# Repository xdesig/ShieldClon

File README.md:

# ShieldClon V 0.00 and 0.01 

## initial versions.

SlieldClon is a board designed, specifically for mClon. It allows secure connections to manipulate the robot. It has the basic components for its operation, as well as access to all free connections to be able to add new elements. The robot with ShieldClon feeds through a 18650 Li-ion battery 3.7V, which you can recharge through the board.
This plate can be complicated to weld by students that do not have much experience, since it has many components and pins very together, but it is a good challenge to learn.
From the mClon team, we consider it important that students understand the robot's internal functioning, who knows their components and what their function is, so we recommend starting from 4th of ESO not to give the plate already welded, unless previously practiced with protoShield. However, shieldClon can be a good option for work with younger students, always inviting them to connect the sensors and actresses on the shield pins themselves.
Is valid to be able to carry out many STEM projects based on Arduino

![RENDER]

### [Assembly manual][Man]
#### Deseñado en Estrimia con agarimo.

## Author and license
* Author: [XDeSIG][TWI01]
* License:
  CERN Open Hardware Licence Version 2 - Weakly Reciprocal"CERN-OHL-W"
  Doc. Attribution-ShareAlike 4.0 International "CCBY-SA4.0"

## More info:
[tecnoloxia.org]
## To buy boards

Developer don't produce boards to sell. Under [_provider_][provider]
directory there are instructions to order yourself.

<!-- links -->
[tecnoloxia.org]: https://tecnoloxia.org/mclon/que-e-mclon/
[CCBY-SA4.0]: http://creativecommons.org/licenses/by-sa/4.0/
[TWI01]: https://twitter.com/xdesig
[RENDER]: https://github.com/xdesig/ShieldClon/blob/master/img/ShieldClon_0_01_34.png
[provider]: https://www.pcbway.com/project/shareproject/W50475ASJ144_NanoClon_001_gerber_f511f448.html
[Man]: https://github.com/xdesig/ShieldClon/blob/master/ShieldClon_0_00/Montaxe_ShielClon.pdf

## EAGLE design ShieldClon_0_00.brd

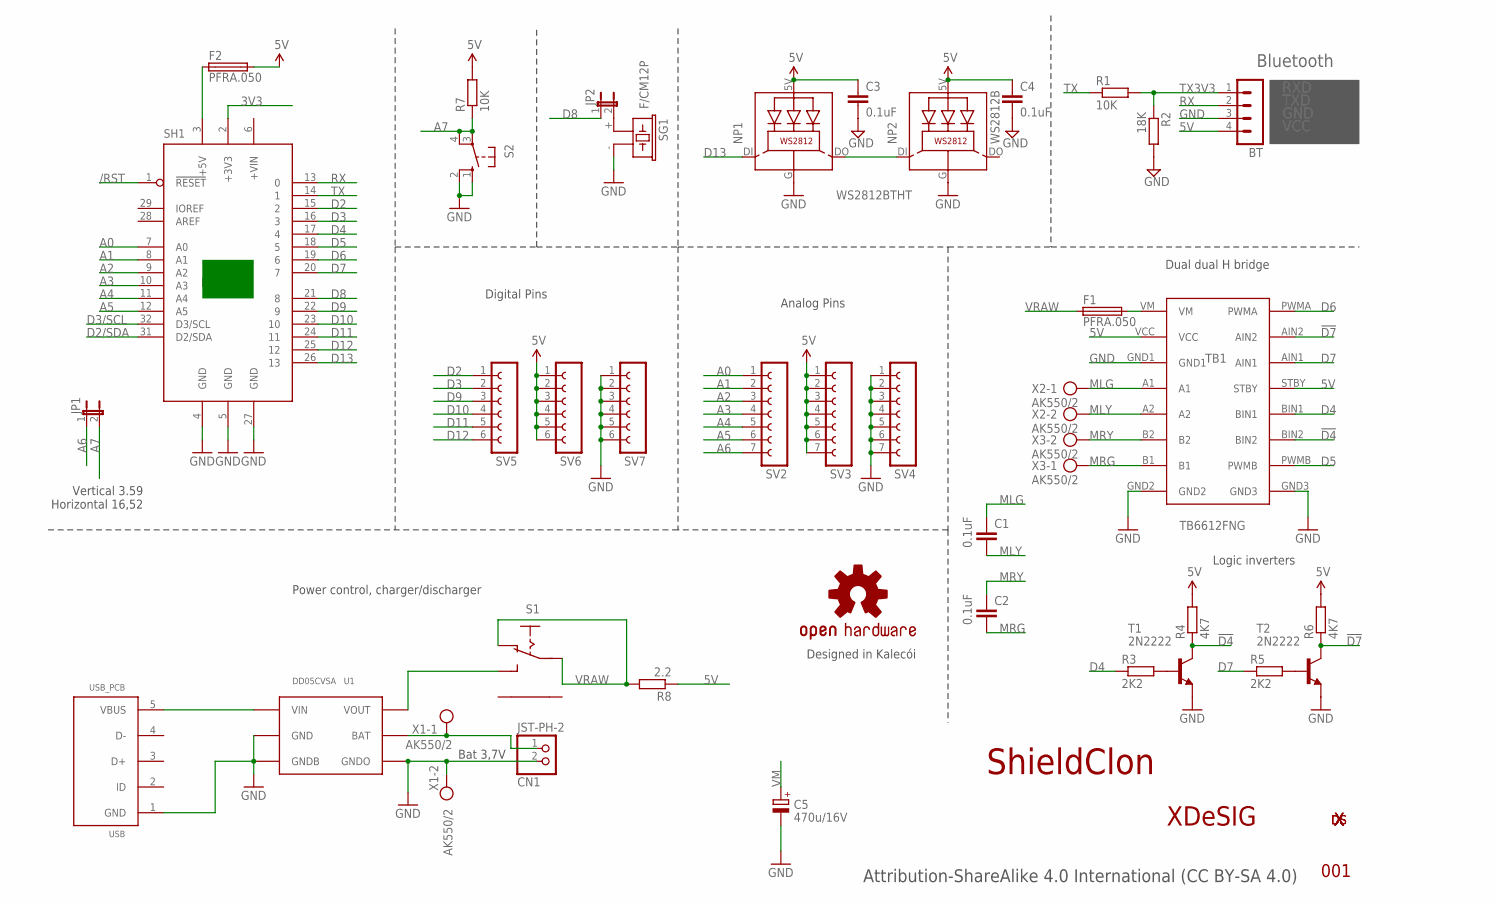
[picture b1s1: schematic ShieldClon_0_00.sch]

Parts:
BT: MA04-1
C1, C2, C3, C4: 0.1uF; C050-024X044
C5: 470u/16V; E2,5-7
CN1: JST-PH-2; JST-PH-2-THM-RA
F1, F2: PFRA.050; TE5
JP1: JP1E; JP1
JP2: JUMPER_JP1E; JUMPER_JP1
LOGO4: OSHW-LOGOS; OSHW-LOGO-S
NP1: WS2812BTHT; NEOPIXEL5MM
NP2: WS2812B; NEOPIXEL5MM
R1, R7: 10K; 0204/7
R2: 18K; 0204/7
R3, R5: 2K2; 0204/7
R4, R6: 4K7; 0204/7
R8: 2.2; 0204/7
S1: ESCORNA_SK12F14D; ESCORNA_SK-12D07
S2: 10-XX; B3F-10XX
SG1: F/CM12P
SH1: ARDUINO_LEONARDO; LEONARDO
SV2, SV3, SV4: FE07-1; FE07
SV5, SV6, SV7: FE06-1; FE06
T1, T2: 2N2222; TO92-EBC-OVAL
TB1: TB6612FNG
U1: DD05CVSA
U$18: XDESIG21; XDESIG
U$19: XDESIG5MM; XDESIG_CU
USB: USB_PCB
X1, X2, X3: AK550/2

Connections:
3V3: SH1.2 (+3V3)
5V: BT.4, C3.1, C4.1, F2.2, NP1.5V (LEDVDD), NP2.5V (LEDVDD), R4.2, R6.2, R7.2, R8.1, SV3.1, SV3.2, SV3.3, SV3.4, SV3.5, SV3.6, SV3.7, SV6.1, SV6.2, SV6.3, SV6.4, SV6.5, SV6.6, TB1.STBY, TB1.VCC
!D4: R4.1, T1.C, TB1.BIN2
!D7: R6.1, T2.C, TB1.AIN2
/RST: SH1.1 (!RESET)
A0: SH1.7 (A0), SV2.1
A1: SH1.8 (A1), SV2.2
A2: SH1.9 (A2), SV2.3
A3: SH1.10 (A3), SV2.4
A4: SH1.11 (A4), SV2.5
A5: SH1.12 (A5), SV2.6
A6: JP1.1, SV2.7
A7: JP1.2, R7.1, S2.3, S2.4 (P1)
D2: SH1.15 (2), SV5.1
D2/SDA: SH1.31 (D2/SDA)
D3: SH1.16 (3), SV5.2
D3/SCL: SH1.32 (D3/SCL)
D4: R3.1, SH1.17 (4), TB1.BIN1
D5: SH1.18 (5), TB1.PWMB
D6: SH1.19 (6), TB1.PWMA
D7: R5.1, SH1.20 (7), TB1.AIN1
D8: JP2.1, SH1.21 (8)
D9: SH1.22 (9), SV5.3
D10: SH1.23 (10), SV5.4
D11: SH1.24 (11), SV5.5
D12: SH1.25 (12), SV5.6
D13: NP1.DI, SH1.26 (13)
GND: BT.3, C3.2, C4.2, C5.-, CN1.2 (1), NP1.G (GND), NP2.G (GND), R2.2, S2.1 (S), S2.2 (S1), SG1.- (2), SH1.4 (GND), SH1.5 (GND), SH1.27 (GND), SV4.1, SV4.2, SV4.3, SV4.4, SV4.5, SV4.6, SV4.7, SV7.1, SV7.2, SV7.3, SV7.4, SV7.5, SV7.6, T1.E, T2.E, TB1.GND1, TB1.GND2, TB1.GND3, U1.P$2 (GND), U1.P$4 (GNDB), U1.P$5 (GNDO), USB.1 (GND), X1.2
MLG: C1.1, TB1.A1, X2.1
MLY: C1.2, TB1.A2, X2.2
MRG: C2.2, TB1.B1, X3.1
MRY: C2.1, TB1.B2, X3.2
unnamed: R3.2, T1.B
unnamed: JP2.2, SG1.+ (1)
unnamed: F2.1, SH1.3 (+5V)
unnamed: R5.2, T2.B
unnamed: U1.P$1 (VIN), USB.5 (VBUS)
unnamed: CN1.1 (2), U1.P$3 (BAT), X1.1
unnamed: NP1.DO, NP2.DI
unnamed: S1.P$3 (S), U1.P$6 (VOUT)
RX: BT.2, SH1.13 (0)
TX: R1.1, SH1.14 (1)
TX3V3: BT.1, R1.2, R2.1
VM: C5.+, F1.2, TB1.VM
VRAW: F1.1, R8.2, S1.P$1, S1.P$2 (O)

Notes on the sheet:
ShieldClon
001
Bluetooth
RXD
TXD
GND
VCC
Vertical 3.59 Horizontal 16,52
XDeSIG
Attribution-ShareAlike 4.0 International (CC BY-SA 4.0)
Bat 3,7V
Digital Pins
Analog Pins
Dual dual H bridge
Logic inverters
Power control, charger/discharger
Designed in Kalecói

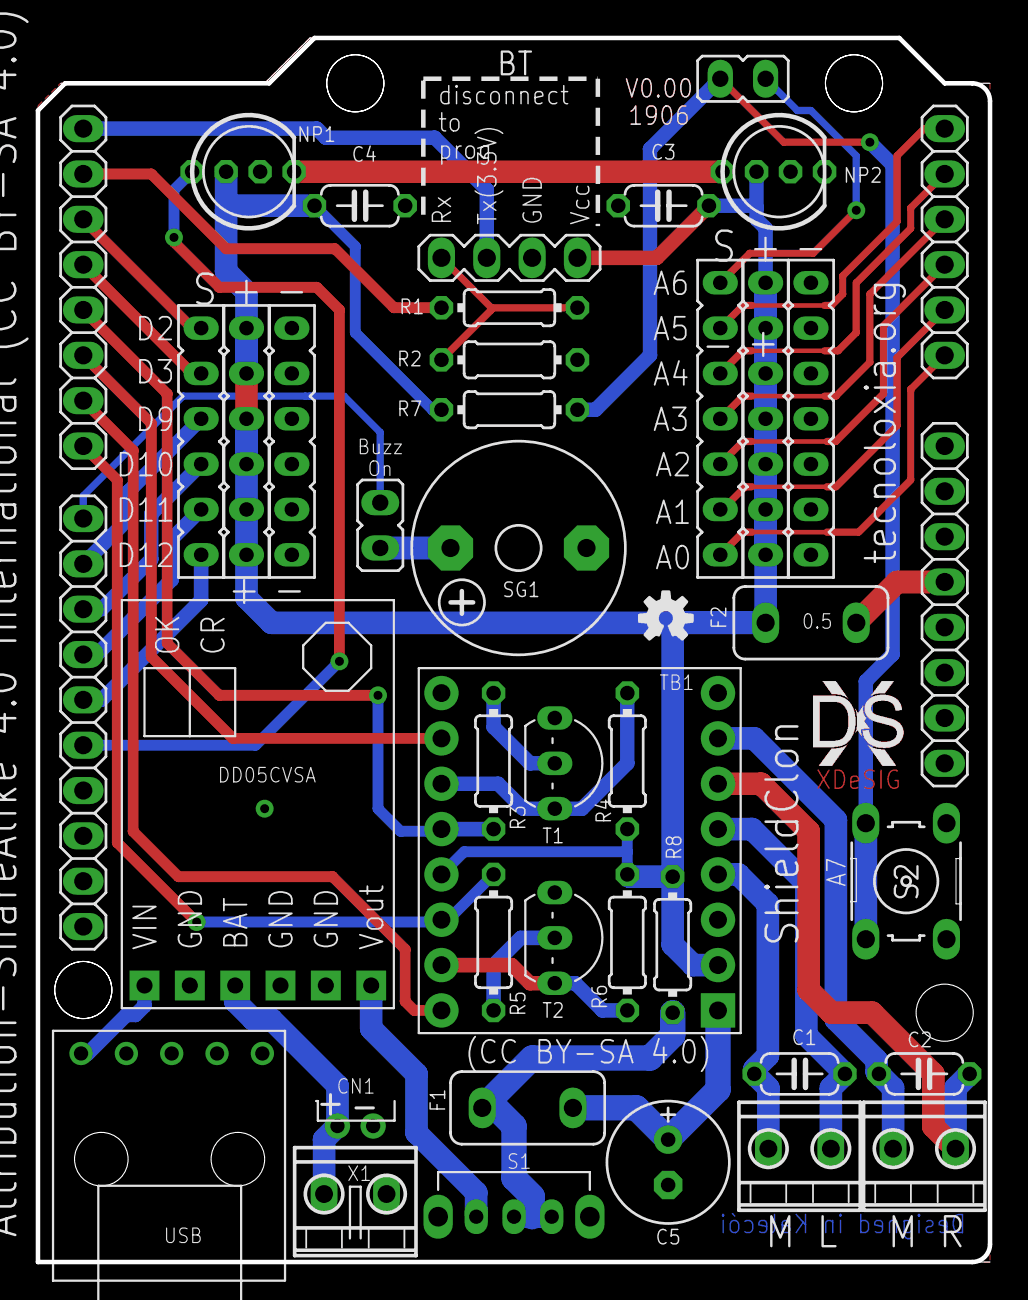
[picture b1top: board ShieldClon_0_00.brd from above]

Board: 2 copper layers, 53.3 x 68.6 mm, 43 parts (1 on the bottom side), 41 nets.

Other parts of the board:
U$21: XDESIG21; XDESIG

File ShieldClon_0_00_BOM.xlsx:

| ShieldClon 00-01 XdeSIG
 | Units | Value | Descr | Package | Parts | LCSC
 | 1 |  | White | 1x6Px2,54 | SV5 | C3329786
 | 1 |  | Red | 1x6Px2,54 | SV6 | C141437
 | 1 |  | Black | 1x6Px2,54 | SV7 | C2337
 | 1 |  | White | 1x7Px2,54 | SV2 | C3329786
 | 1 |  | Red | 1x7Px2,54 | SV3 | C141437
 | 1 |  | Black | 1x7Px2,54 | SV4 | C2337
 | 2 |  | + 1 cap | 1x2Px2,54 | JP1,JP2 | C376075
 | 1 |  | MA04-1 | 1x4Px2,54 Female | BT | C2718488
 | 4 | 0.1uF | C-EU025-024X044 | C025-024X044 | C1,, C4 | C353903
 | 2 | 10K | R-EU_0204/7 | 0204/7 | R1, R7 | C61299
 | 1 | 18K | R-EU_0204/7 | 0204/7 | R2 | C70811
 | 1 | 2.2 | R-EU_0204/7 | 0204/7 | R8 | C2894548
 | 2 | 2K2 | R-EU_0204/7 | 0204/7 | R3, R5 | C120063
 | 2 | 4K7 | R-EU_0204/7 | 0204/7 | R4, R6 | C120071
 | 2 | 2N2222 | 2N2222 | TO92-EBC-OVAL | T1, T2 | C5330385
 | 1 | 470u/16V | 470uF 16V | E2,5-7 | C5 | C2960374
 | 3 | AK550/2 | AK550/2 | AK550/2 3,5mm | X1, X2, X3 | C784940
 | 1 | F/CM12P | BUZZER 12mm (7mm) | F/CM12P | SG1 | C2689171
 | 2 | PFRA.050 | Polyfuse 0.65A | TE5 | F1, F2 | C1562414
 | 1 | TB6612FNG | TB6612FNG on PCB | TB6612FNG | TB1 |  | Aliexpress
 | 1 | USB_PCB | Micro USB | MicroXNJ | USB |  | Aliexpress
 | 2 | WS2812B | WS2812BTHT | NEOPIXEL5MM | NP2 |  | sparkfun
 | Charger/step up option
 | 1 | DD05CVSA | DD05CVSA | DD05CVSA | U1 |  | aliexpress

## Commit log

2019-02-12 Bom added
2019-02-14 add mount guide
2019-02-14 Add Assembly guide
2019-02-15 BOM ODS add
2020-05-30 Add BOM .odt
2023-03-13 Update BOM
2023-05-20 Update Certification

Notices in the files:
ShieldClon_0_00.brd:
Attribution-ShareAlike 4.0 International (CC BY-SA 4.0)  XDeSIG
parts and their libraries:
SparkFun-Aesthetics: Licensing: CC v3.0 Share-Alike You are welcome to use this library for commercial purposes.
